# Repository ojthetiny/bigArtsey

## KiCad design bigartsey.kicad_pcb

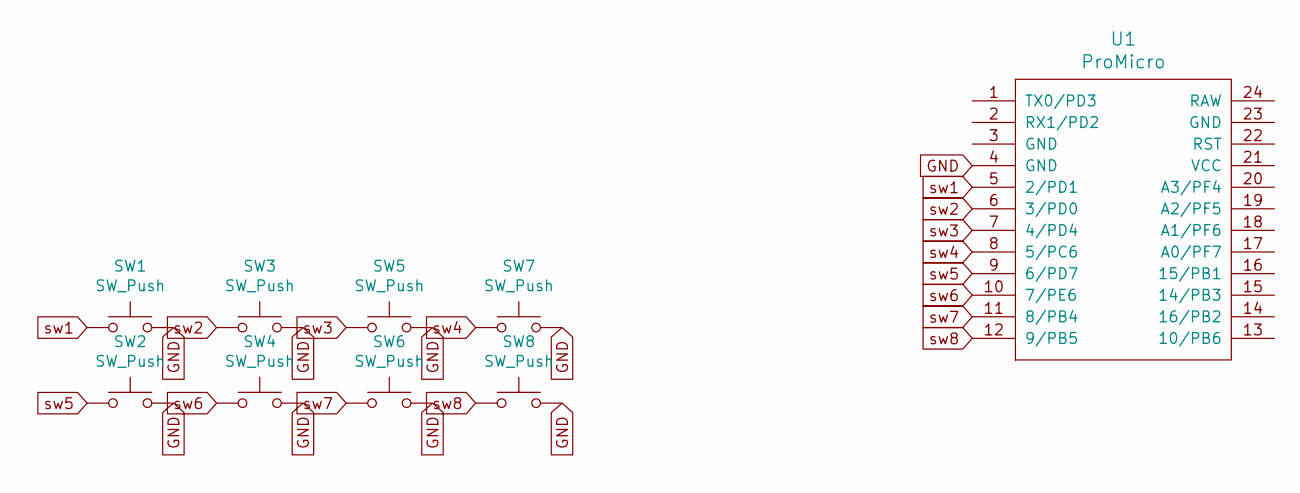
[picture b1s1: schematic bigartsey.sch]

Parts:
SW1, SW2, SW3, SW4, SW5, SW6, SW7, SW8: SW_Push; kailh_big_series
U1: ProMicro; ArduinoProMicro

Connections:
GND: SW1.2, SW2.2, SW3.2, SW4.2, SW5.2, SW6.2, SW7.2, SW8.2, U1.4 (GND)
sw1: SW1.1, U1.5 (2/PD1)
sw2: SW3.1, U1.6 (3/PD0)
sw3: SW5.1, U1.7 (4/PD4)
sw4: SW7.1, U1.8 (5/PC6)
sw5: SW2.1, U1.9 (6/PD7)
sw6: SW4.1, U1.10 (7/PE6)
sw7: SW6.1, U1.11 (8/PB4)
sw8: SW8.1, U1.12 (9/PB5)

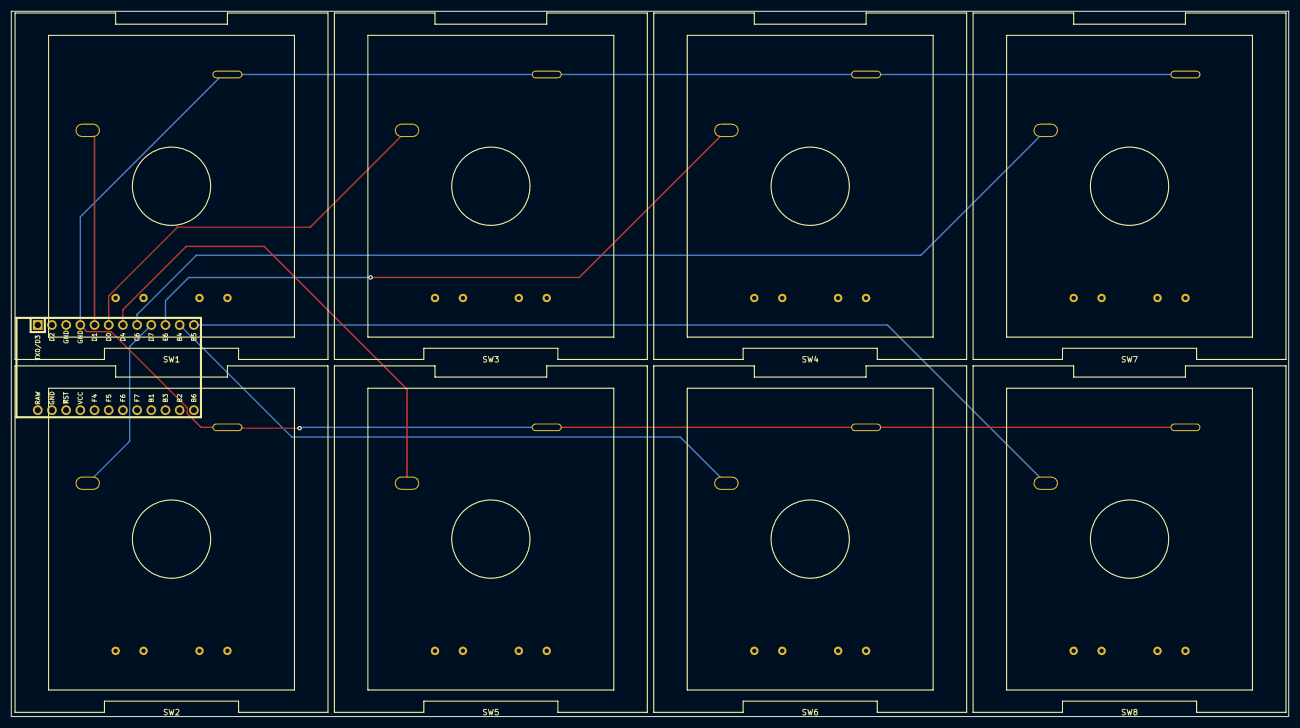
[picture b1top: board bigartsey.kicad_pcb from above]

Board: 2 copper layers, 228.6 x 126.2 mm, 9 parts (1 on the bottom side), 9 nets.

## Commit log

2021-01-26 Initial commit
    eat shit and die :3
